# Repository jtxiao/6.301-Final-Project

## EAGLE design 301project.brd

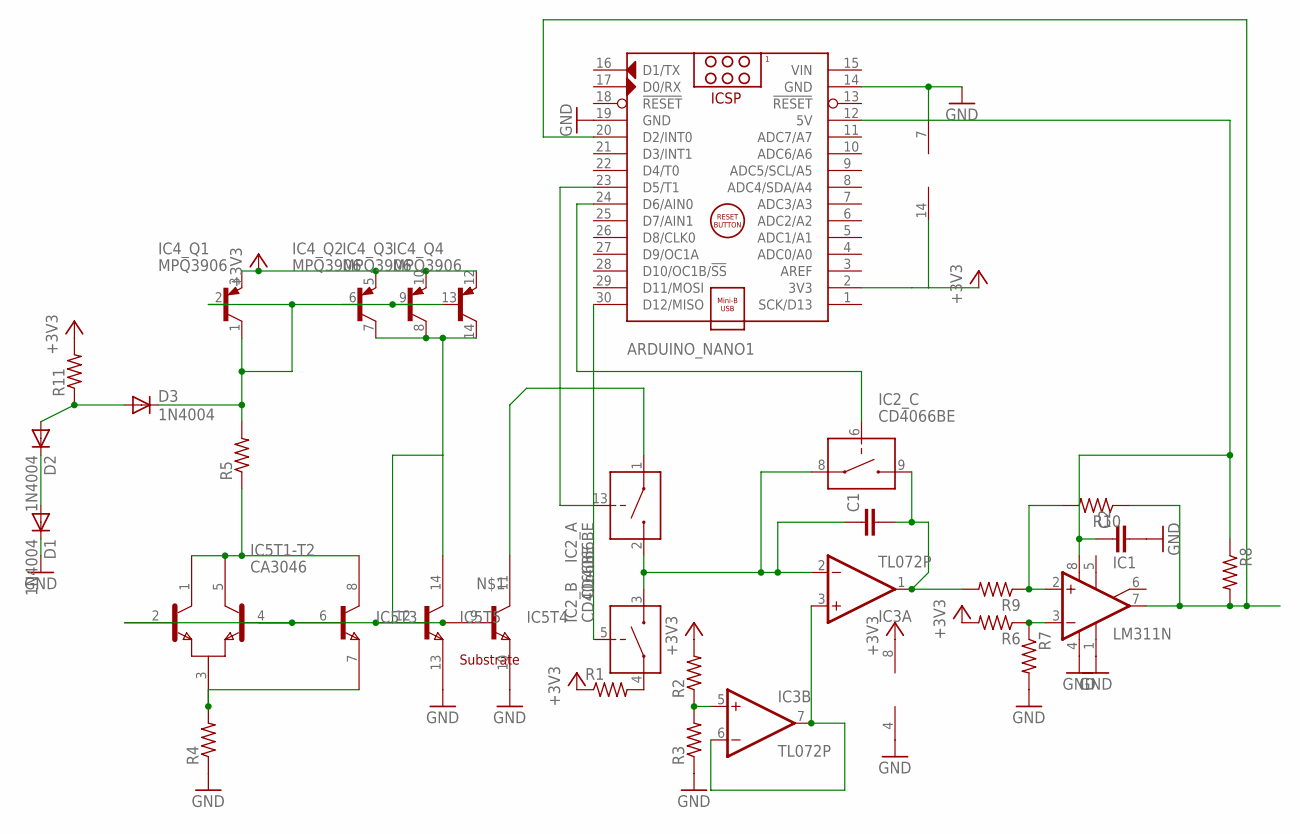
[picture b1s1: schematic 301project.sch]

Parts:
ARDUINO_NANO1: ARDUINO_NANO
C1, C2: C5/2.5; C5B2.5
D1, D2, D3: 1N4004; DO41-10
IC1: LM311N; DIL08
IC2: CD4066BE; DIL14
IC3: TL072P; DIL08
IC4: MPQ3906; DIL14
IC5: CA3046; DIL14
R1, R2, R3, R4, R5, R6, R7, R8, R9, R10, R11: R-US_0204/7; 0204/7

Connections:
+3V3: ARDUINO_NANO1.2 (3V3), IC2.14 (V+), IC3.8 (V+), IC4.3 (E), IC4.5 (E), IC4.10 (E), IC4.12 (E), R1.1, R2.2, R6.2, R11.2
GND: ARDUINO_NANO1.14 (GND), ARDUINO_NANO1.19 (GND), C2.2, D1.C, IC1.1 (GND), IC1.4 (V-), IC2.7 (V-), IC3.4 (V-), IC5.10 (E), IC5.13 (E), R3.1, R4.1, R7.2
unnamed: IC4.7 (C), IC4.8 (C), IC4.14 (C), IC5.2 (B1), IC5.6 (B), IC5.12 (B), IC5.14 (C)
unnamed: C1.1, IC2.2 (IN/OUT2), IC2.3 (IN/OUT2), IC2.8 (IN/OUT1), IC3.2 (-IN)
unnamed: D3.C, IC4.1 (C), IC4.2 (B), IC4.6 (B), IC4.9 (B), IC4.13 (B), R5.2
unnamed: ARDUINO_NANO1.23 (D5/T1), IC2.13 (CONTROL)
unnamed: IC5.3 (E), IC5.7 (E), R4.2
unnamed: IC5.1 (C1), IC5.5 (C2), IC5.8 (C), R5.1
unnamed: ARDUINO_NANO1.30 (D12/MISO), IC2.5 (CONTROL)
unnamed: IC2.1 (IN/OUT1), IC5.11 (C)
unnamed: IC3.3 (+IN), IC3.6 (-IN), IC3.7 (OUT)
unnamed: IC2.4 (IN/OUT1), R1.2
unnamed: IC3.5 (+IN), R2.1, R3.2
unnamed: ARDUINO_NANO1.20 (D2/INT0), IC1.7 (OUT), R8.2, R10.1
unnamed: C1.2, IC2.9 (IN/OUT2), IC3.1 (OUT), R9.2
unnamed: ARDUINO_NANO1.24 (D6/AIN0), IC2.6 (CONTROL)
unnamed: IC1.3 (-IN), R6.1, R7.1
unnamed: D1.A, D2.C
unnamed: IC1.2 (+IN), R9.1, R10.2
unnamed: ARDUINO_NANO1.12 (5V), C2.1, IC1.8 (V+), R8.1
unnamed: D2.A, D3.A, R11.1
VIN: ARDUINO_NANO1.15 (VIN)

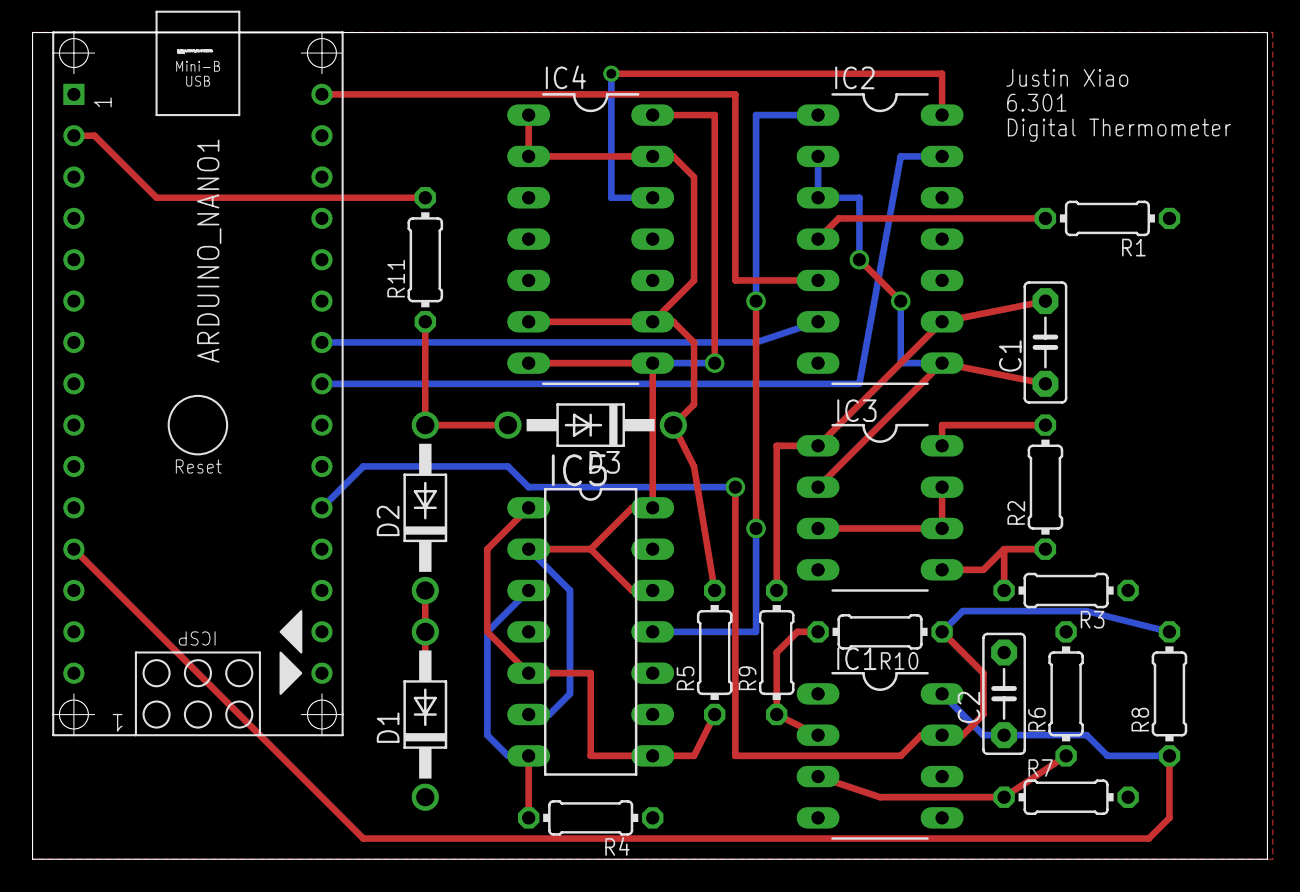
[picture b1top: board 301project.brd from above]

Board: 2 copper layers, 75.9 x 50.8 mm, 22 parts (0 on the bottom side), 21 nets.

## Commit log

2016-12-13 added PCB files
